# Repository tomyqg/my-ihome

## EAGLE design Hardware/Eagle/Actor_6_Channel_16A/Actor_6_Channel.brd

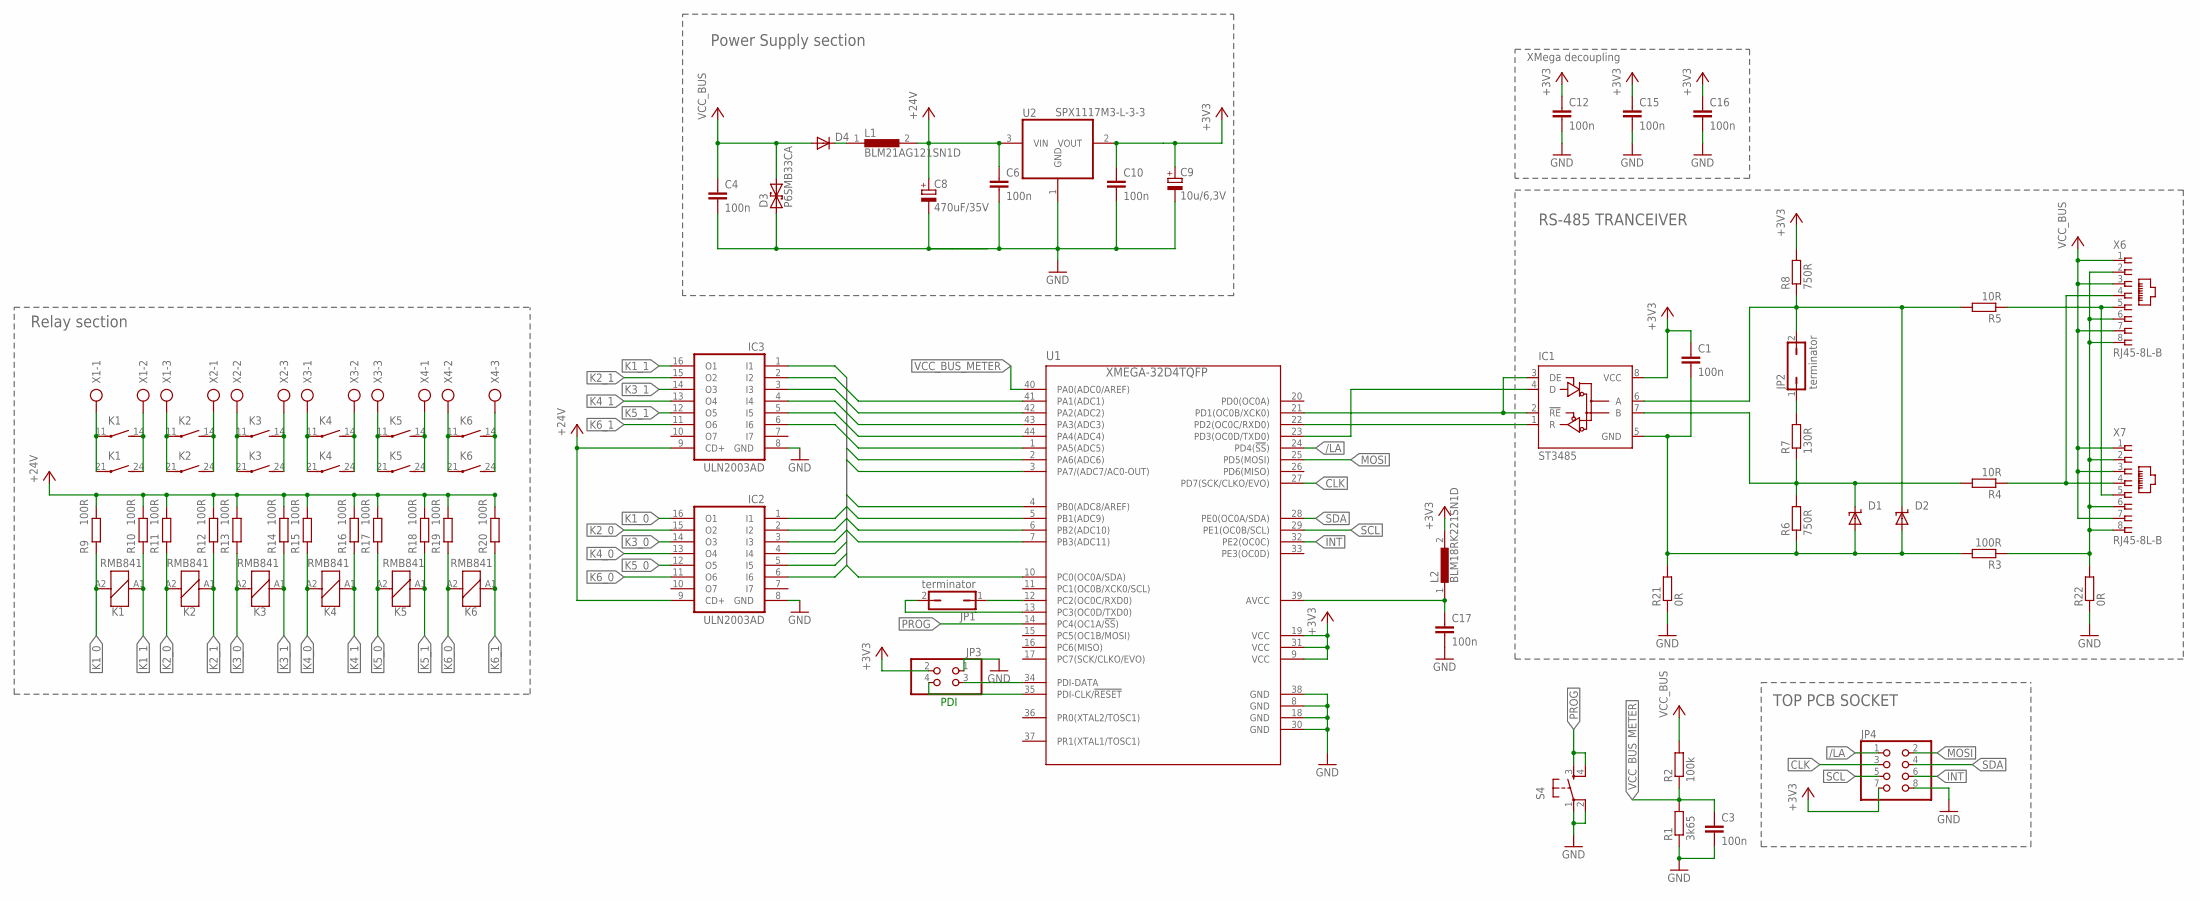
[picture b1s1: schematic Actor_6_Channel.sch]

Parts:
C1, C3, C4, C6, C10, C12, C15, C16, C17: 100n; C0603K
C8: 470uF/35V; E5-10,5
C9: 10u/6,3V; E2-4
D1, D2: SUPPRESSOR-SMBJ; SMBJ
D3: P6SMB33CA; DO214AA
D4: DIODE-DO214AA; DO214AA
IC1: ST3485; D_R-PDSO-G8
IC2, IC3: ULN2003AD; SO16
JP1, JP2: terminator; JP1
JP3: PINHD-2X2; 2X02
JP4: PINHD-2X4; 2X04
K1, K2, K3, K4, K5, K6: RMB841; RT2N/O
L1: BLM21AG121SN1D; 805
L2: BLM18RK221SN1D; 0603
R1: 3k65; R0603
R2: 100k; R0603
R3, R9, R10, R11, R12, R13, R14, R15, R16, R17, R18, R19, R20: 100R; R0603
R4, R5: 10R; R0603
R6: 750R; M1206
R7: 130R; R0603
R8: 750R; R0603
R21, R22: 0R; R0603
S4: SPARKFUN_TAC_SWITCHPTH; SPARKFUN_TACTILE-PTH
U1: XMEGA-32D4TQFP; TQFP44
U2: SPX1117M3-L-3-3; SOT223
X1, X2, X3, X4: MKDS_5/3-7,5; MKDS_5/-750
X6, X7: RJ45-8L-B; RJ45-NO-SHIELD

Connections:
+3V3: C1.1, C9.+, C10.1, C12.1, C15.1, C16.1, IC1.8 (VCC), JP3.2, JP4.7, L2.2, R8.2, U1.9 (VCC), U1.19 (VCC), U1.31 (VCC), U2.2 (VOUT)
+24V: C6.1, C8.+, IC2.9 (CD+), IC3.9 (CD+), L1.2, R9.2, R10.2, R11.2, R12.2, R13.2, R14.2, R15.2, R16.2, R17.2, R18.2, R19.2, R20.2, U2.3 (VIN)
/LA: JP4.1, U1.24 (PD4(!SS!))
A: R5.1, X6.5, X7.5
B: R4.1, X6.4, X7.4
CLK: JP4.3, U1.27 (PD7(SCK/CLKO/EVO))
DE_/RE: IC1.2 (!RE), IC1.3 (DE), U1.21 (PD1(OC0B/XCK0))
GND: C3.2, C4.2, C6.2, C8.-, C9.-, C10.2, C12.2, C15.2, C16.2, C17.2, D3.A (1), IC2.8 (GND), IC3.8 (GND), JP3.1, JP4.8, R1.1, R21.1, R22.1, S4.1, S4.2, U1.8 (GND), U1.18 (GND), U1.30 (GND), U1.38 (GND), U2.1 (GND)
INT: JP4.6, U1.32 (PE2(OC0C))
K1_0: IC2.16 (O1), K1.A2 (1), R9.1
K1_1: IC3.16 (O1), K1.A1 (2), R10.1
K2_0: IC2.15 (O2), K2.A2 (1), R11.1
K2_1: IC3.15 (O2), K2.A1 (2), R12.1
K3_0: IC2.14 (O3), K3.A2 (1), R13.1
K3_1: IC3.14 (O3), K3.A1 (2), R14.1
K4_0: IC2.13 (O4), K4.A2 (1), R15.1
K4_1: IC3.13 (O4), K4.A1 (2), R16.1
K5_0: IC2.12 (O5), K5.A2 (1), R17.1
K5_1: IC3.12 (O5), K5.A1 (2), R18.1
K6_0: IC2.11 (O6), K6.A2 (1), R19.1
K6_1: IC3.11 (O6), K6.A1 (2), R20.1
MOSI: JP4.2, U1.25 (PD5(MOSI))
unnamed: K1.11, K1.21, X1.1
unnamed: K6.11, K6.21, X4.2
unnamed: K2.14 (S), K2.24 (S), X2.1
unnamed: K2.11, K2.21, X1.3
unnamed: K3.11, K3.21, X2.2
unnamed: K3.14 (S), K3.24 (S), X2.3
unnamed: K4.11, K4.21, X3.1
unnamed: K5.11, K5.21, X3.3
unnamed: K5.14 (S), K5.24 (S), X4.1
unnamed: JP3.3, U1.34 (PDI-DATA)
unnamed: K6.14 (S), K6.24 (S), X4.3
unnamed: JP3.4, U1.35 (PDI-CLK/!RESET)
unnamed: JP2.1, R7.2
unnamed: D1.C, IC1.7 (B), R4.2, R6.2, R7.1
unnamed: D4.C, L1.1
unnamed: JP1.2, U1.13 (PC3(OC0D/TXD0))
unnamed: JP1.1, U1.12 (PC2(OC0C/RXD0))
unnamed: C17.1, L2.1, U1.39 (AVCC)
unnamed: C1.2, D1.A, D2.A, IC1.5 (GND), R3.2, R6.1, R21.2
unnamed: R3.1, R22.2, X6.2, X6.6, X6.8, X7.2, X7.6, X7.8
unnamed: K1.14 (S), K1.24 (S), X1.2
unnamed: K4.14 (S), K4.24 (S), X3.2
PA1: IC3.6 (I6), U1.41 (PA1(ADC1))
PA2: IC3.5 (I5), U1.42 (PA2(ADC2))
PA3: IC3.4 (I4), U1.43 (PA3(ADC3))
PA4: IC3.3 (I3), U1.44 (PA4(ADC4))
PA5: IC3.2 (I2), U1.1 (PA5(ADC5))
PA6: IC3.1 (I1), U1.2 (PA6(ADC6))
PA7: IC2.6 (I6), U1.3 (PA7/(ADC7/AC0-OUT))
PB0: IC2.5 (I5), U1.4 (PB0(ADC8/AREF))
PB1: IC2.4 (I4), U1.5 (PB1(ADC9))
PB2: IC2.3 (I3), U1.6 (PB2(ADC10))
PB3: IC2.2 (I2), U1.7 (PB3(ADC11))
PC0: IC2.1 (I1), U1.10 (PC0(OC0A/SDA))
PROG: S4.3, S4.4, U1.14 (PC4(OC1A/!SS!))
RS485_A1: D2.C, IC1.6 (A), JP2.2, R5.2, R8.1
RXD: IC1.1 (R), U1.22 (PD2(OC0C/RXD0))
SCL: JP4.5, U1.29 (PE1(OC0B/SCL))
SDA: JP4.4, U1.28 (PE0(OC0A/SDA))
TXD: IC1.4 (D), U1.23 (PD3(OC0D/TXD0))
VCC_BUS: C4.1, D3.C (2), D4.A, R2.2, X6.1, X6.3, X6.7, X7.1, X7.3, X7.7
VCC_BUS_METER: C3.1, R1.2, R2.1, U1.40 (PA0(ADC0/AREF))

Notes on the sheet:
Power Supply section
XMega decoupling
RS-485 TRANCEIVER
PDI
Relay section
TOP PCB SOCKET

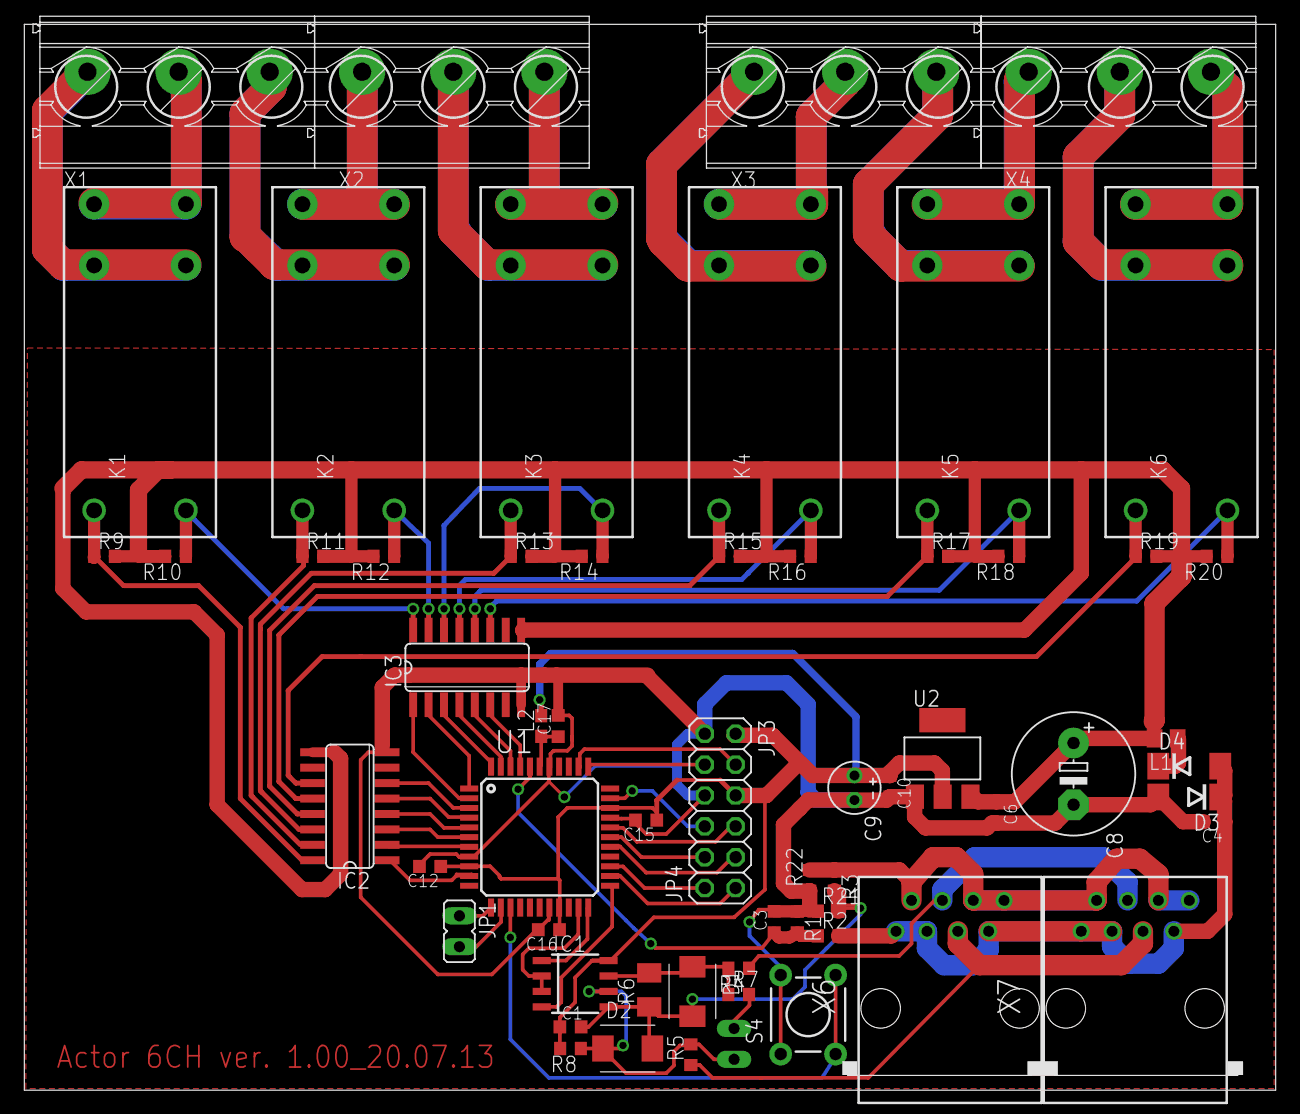
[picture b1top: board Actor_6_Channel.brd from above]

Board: 2 copper layers, 103.0 x 87.7 mm, 61 parts (1 on the bottom side), 64 nets.

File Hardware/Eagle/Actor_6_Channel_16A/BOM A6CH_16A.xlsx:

Part | Value | Package | Price (>100pcs) brutto | Supplier | %
C1 | 100n | C0603K | 2.5000000000000001E-2 | TME | 1.4651155976206517E-2
C2 | 470uF/35V | E5-10,5 | 0.27 | TME | 0.15823248454303038
C3 | 100n | C0603K | 2.5000000000000001E-2 | TME | 1.4651155976206517E-2
C4 | 100n | C0603K | 2.5000000000000001E-2 | TME | 1.4651155976206517E-2
C5 | 10u/6,3V | E2-5 | 5.7000000000000002E-2 | TME | 3.3404635625750856E-2
C6 | 100n | C0603K | 2.5000000000000001E-2 | TME | 1.4651155976206517E-2
C7 | 100n | C0603K | 2.5000000000000001E-2 | TME | 1.4651155976206517E-2
C8 | 100n | C0603K | 2.5000000000000001E-2 | TME | 1.4651155976206517E-2
C9 | 100n | C0603K | 2.5000000000000001E-2 | TME | 1.4651155976206517E-2
C10 | 100n | C0603K | 2.5000000000000001E-2 | TME | 1.4651155976206517E-2
C11 | 100n | C0603K | 2.5000000000000001E-2 | TME | 1.4651155976206517E-2
D1 | P6SMB6.8CA-LF | DO214AA | 0.5 | TME | 0.29302311952413035
D2 | P6SMB6.8CA-LF | DO214AA | 0.5 | TME | 0.29302311952413035
D3 | P6SMB33CA | DO214AA | 0.43 | TME | 0.25199988279075208
D4 |  | DO214AA | 0.1 | TME | 5.860462390482607E-2
IC1 | ST3485 | D_R-PDSO-G8 | 3.3 | TME | 1.9339525888592599
IC2 | ULN2003AD | SO16 | 0.72 | TME | 0.42195329211474769
IC3 | ULN2003AD | SO16 | 0.72 | TME | 0.42195329211474769
JP1 | terminator | JP1 | 6.8000000000000005E-2 | TME | 3.9851144255281724E-2
JP2 | terminator | JP1 | 6.8000000000000005E-2 | TME | 3.9851144255281724E-2
JP3 |  | 2X02 | 0.13600000000000001 | TME | 7.9702288510563449E-2
JP4 |  | 2X04 | 0.27200000000000002 | TME | 0.1594045770211269
K1 | RMB841 | RT2N/O | 14.32 | piekarz | 8.3921821431710928
K2 | RMB841 | RT2N/O | 14.32 | piekarz | 8.3921821431710928
K3 | RMB841 | RT2N/O | 14.32 | piekarz | 8.3921821431710928
K4 | RMB841 | RT2N/O | 14.32 | piekarz | 8.3921821431710928
K5 | RMB841 | RT2N/O | 14.32 | piekarz | 8.3921821431710928
K6 | RMB841 | RT2N/O | 14.32 | piekarz | 8.3921821431710928
L1 | BLM21AG121 | 805 | 0.222 | TME | 0.13010226506871386
L2 | BLM18RK221 | 603 | 9.7000000000000003E-2 | TME | 5.6846485187681289E-2
R1 | 3k65 | R0603 | 2.5000000000000001E-2 | TME | 1.4651155976206517E-2
R2 | 100k | R0603 | 2.5000000000000001E-2 | TME | 1.4651155976206517E-2
R3 | 100R | R0603 | 2.5000000000000001E-2 | TME | 1.4651155976206517E-2
R4 | 10R | R0603 | 2.5000000000000001E-2 | TME | 1.4651155976206517E-2
R5 | 10R | R0603 | 2.5000000000000001E-2 | TME | 1.4651155976206517E-2
R6 | 750R | M1206 | 2.5000000000000001E-2 | TME | 1.4651155976206517E-2
R7 | 130R | R0603 | 2.5000000000000001E-2 | TME | 1.4651155976206517E-2
R8 | 750R | R0603 | 2.5000000000000001E-2 | TME | 1.4651155976206517E-2
R9 | 100R | R0603 | 2.5000000000000001E-2 | TME | 1.4651155976206517E-2
R10 | 100R | R0603 | 2.5000000000000001E-2 | TME | 1.4651155976206517E-2
R11 | 100R | R0603 | 2.5000000000000001E-2 | TME | 1.4651155976206517E-2
R12 | 100R | R0603 | 2.5000000000000001E-2 | TME | 1.4651155976206517E-2
R13 | 100R | R0603 | 2.5000000000000001E-2 | TME | 1.4651155976206517E-2
R14 | 100R | R0603 | 2.5000000000000001E-2 | TME | 1.4651155976206517E-2
R15 | 100R | R0603 | 2.5000000000000001E-2 | TME | 1.4651155976206517E-2
R16 | 100R | R0603 | 2.5000000000000001E-2 | TME | 1.4651155976206517E-2
R17 | 100R | R0603 | 2.5000000000000001E-2 | TME | 1.4651155976206517E-2
R18 | 100R | R0603 | 2.5000000000000001E-2 | TME | 1.4651155976206517E-2
R19 | 100R | R0603 | 2.5000000000000001E-2 | TME | 1.4651155976206517E-2
R20 | 100R | R0603 | 2.5000000000000001E-2 | TME | 1.4651155976206517E-2
R21 | 0R | R0603 | 2.5000000000000001E-2 | TME | 1.4651155976206517E-2
R22 | 0R | R0603 | 2.5000000000000001E-2 | TME | 1.4651155976206517E-2
S4 |  | NINIGI TACTM-619P-F | 0.24 | TME | 0.14065109737158255
U1 | XMEGA-32D4 | TQFP44 | 9.6300000000000008 | TME | 5.6436252820347503
U2 | SPX1117M3- | SOT223 | 0.63 | TME | 0.36920913060040422
X1 |  | TB-7.5-3P | 0.63 | TME | 0.36920913060040422
X2 |  | TB-7.5-3P | 0.63 | TME | 0.36920913060040422
X3 |  | TB-7.5-3P | 0.63 | TME | 0.36920913060040422
X4 |  | TB-7.5-3P | 0.63 | TME | 0.36920913060040422
X5 | RJ45-8L-B | RJ45-NO-SHIELD | 1.61 | TME | 0.94353444486769966
X6 | RJ45-8L-B | RJ45-NO-SHIELD | 1.61 | TME | 0.94353444486769966
Case |  | MODULBOX | 39.24 | TME | 22.996454420253748
PCB |  |  | 21 | drukowane.pl | 12.306971020013474
 |  | amount | 170.63500000000008

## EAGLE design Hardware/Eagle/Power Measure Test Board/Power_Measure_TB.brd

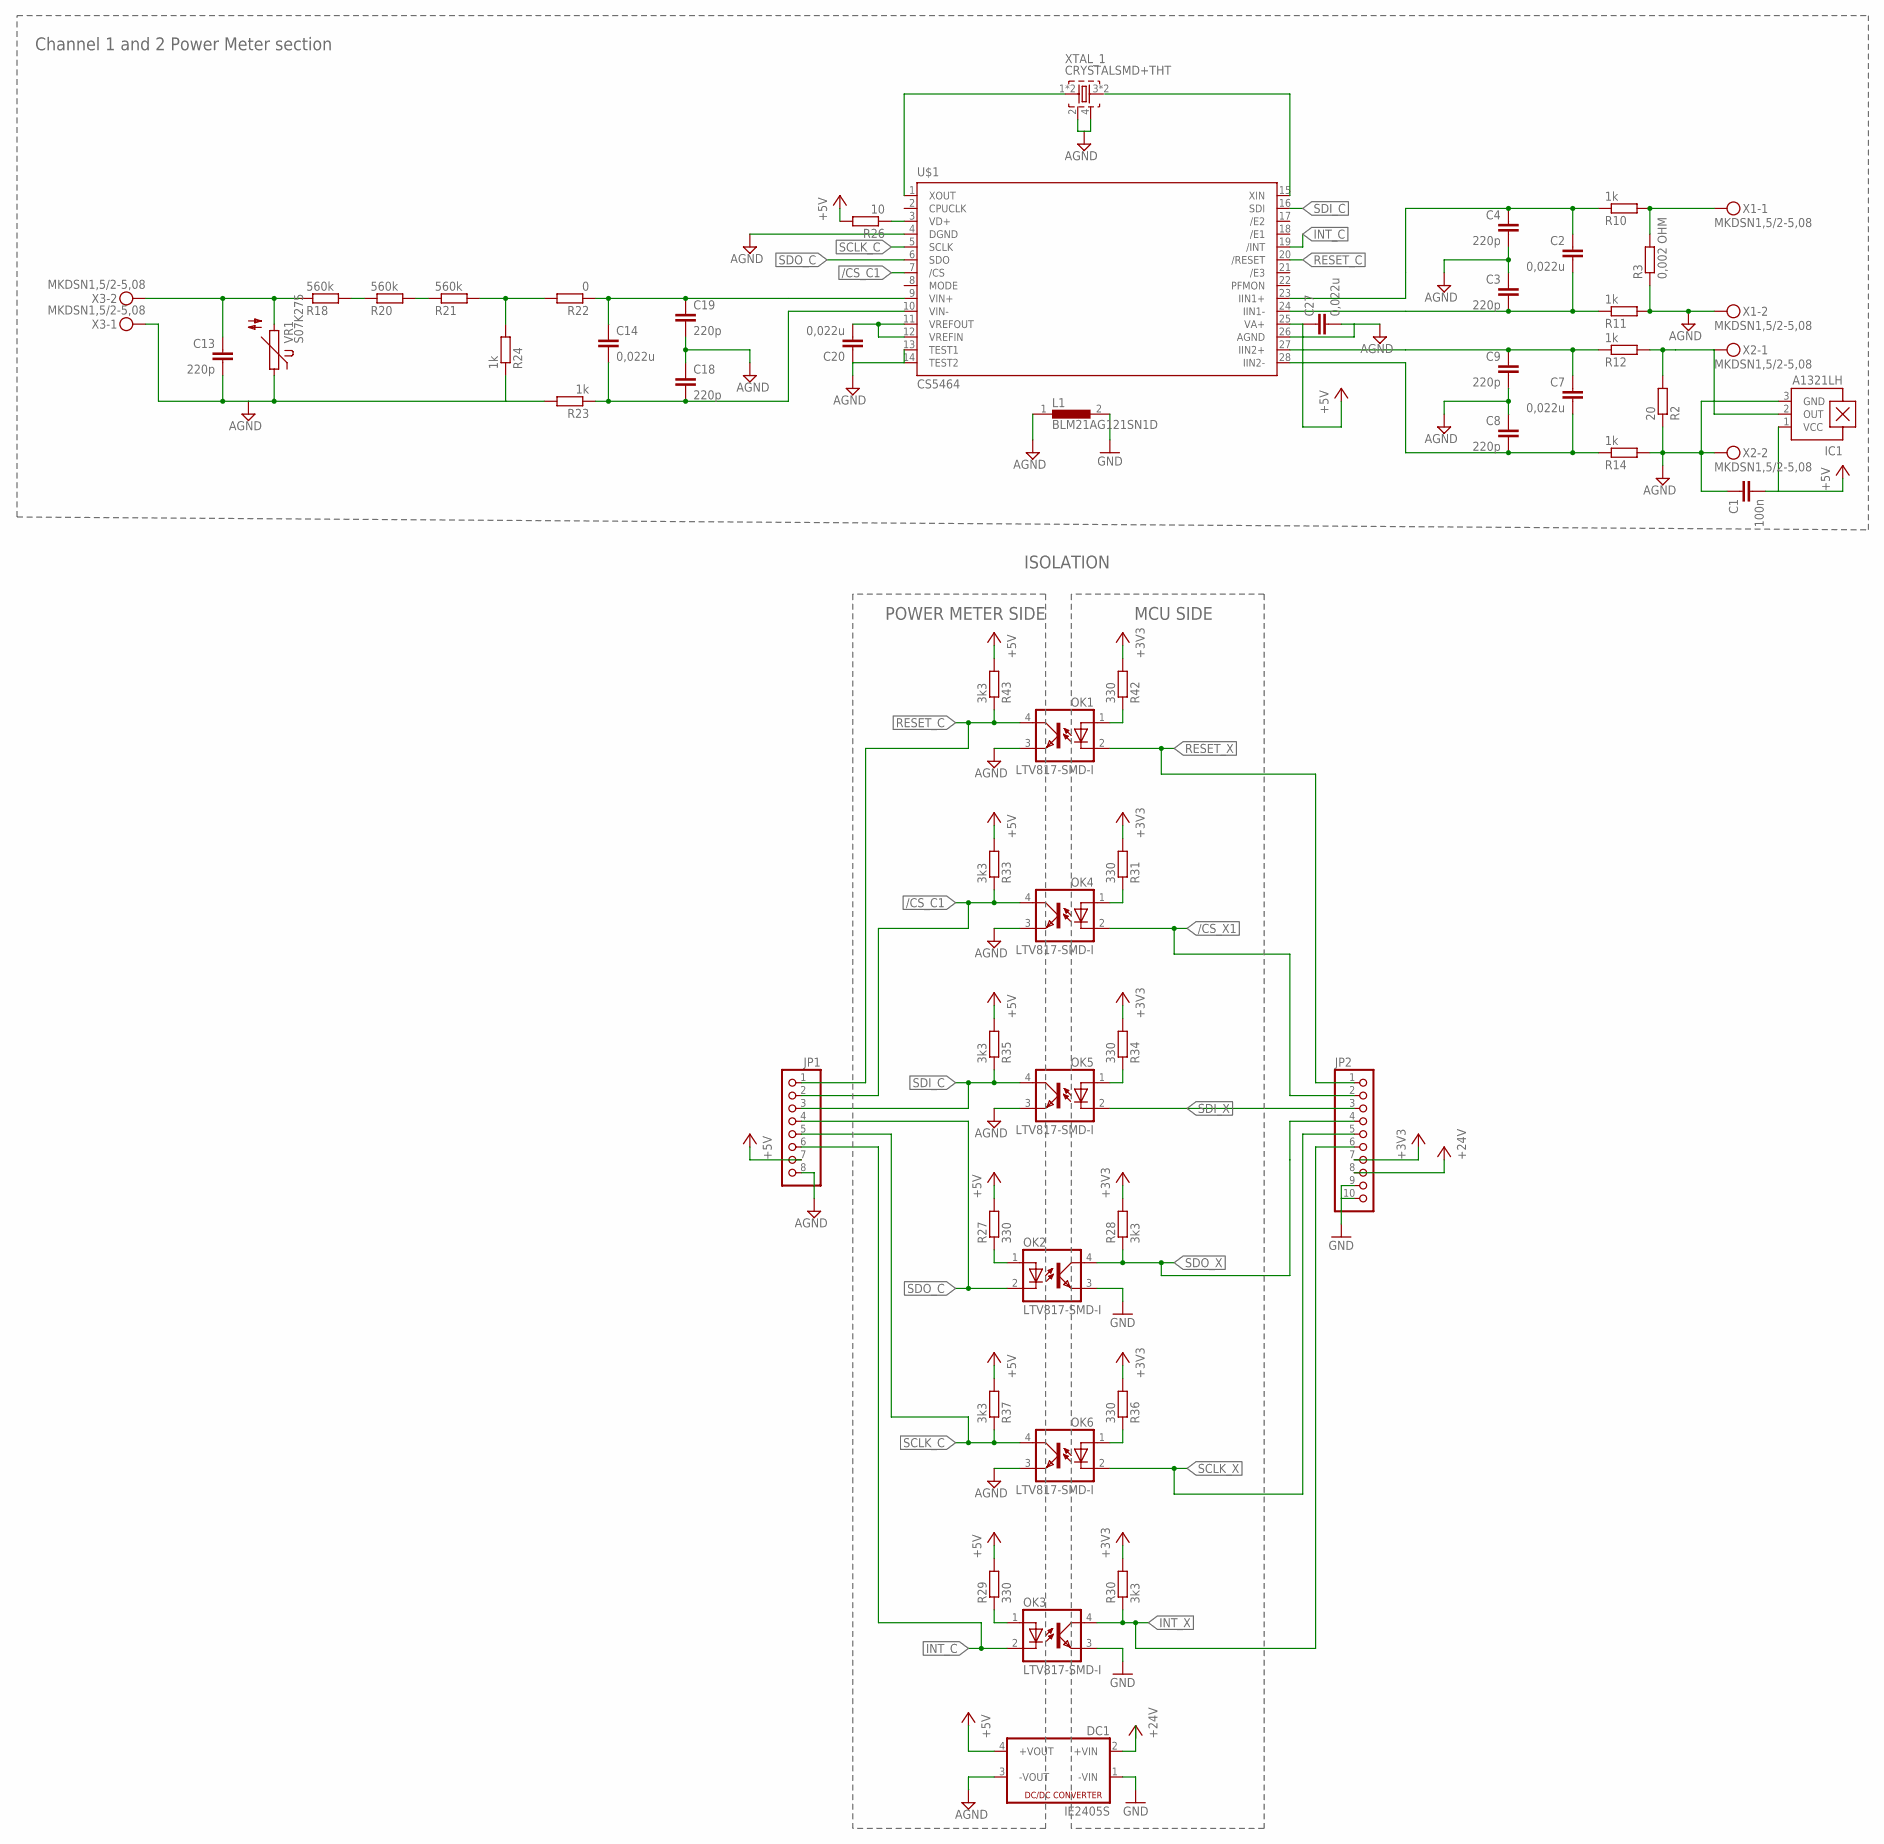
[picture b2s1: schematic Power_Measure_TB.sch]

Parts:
C1: 100n; C0603K
C2, C7, C14, C20, C27: 0,022u; C0603K
C3, C4, C8, C9, C13, C18, C19: 220p; C0603K
DC1: IE2405S; 4SIL
IC1: A1321LH; SOT23-W
JP1: PINHD-1X8; 1X08
JP2: PINHD-1X10; 1X10
L1: BLM21AG121SN1D; 805
OK1, OK2, OK3, OK4, OK5, OK6: LTV817-SMD-I; SMD4
R2: 20; R0603
R3: 0,002 OHM; R2512
R10, R11, R12, R14, R23, R24: 1k; R0603
R18, R20, R21: 560k; R0603
R22: 0; R0603
R26: 10; R0603
R27, R29, R31, R34, R36, R42: 330; M0805
R28, R30, R33, R35, R37, R43: 3k3; M0805
U$1: CS5464; SSOP-28L
VR1: S07K275
X1, X2, X3: MKDSN1,5/2-5,08
XTAL_1: CRYSTALSMD+THT; CRYSTAL20H+MT38

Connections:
+3V3: C1.2, IC1.1 (VCC), JP1.7, JP2.7, R28.2, R30.2, R31.2, R34.2, R36.2, R42.2
+5V: C27.1, DC1.4 (+VOUT), R26.2, R27.2, R29.2, R33.2, R35.2, R37.2, R43.2, U$1.25 (VA+)
/CS_C1: JP1.2, OK4.4 (COL), R33.1, U$1.7 (/CS)
/CS_X1: JP2.2, OK4.2 (C)
AGND: C1.1, C3.1, C4.2, C8.1, C9.2, C13.2, C18.1, C19.2, C20.1, C27.2, DC1.3 (-VOUT), IC1.3 (GND), JP1.8, L1.1, OK1.3 (EMIT), OK4.3 (EMIT), OK5.3 (EMIT), OK6.3 (EMIT), R2.1, R3.1, R11.2, R14.2, R23.2, R24.1, U$1.4 (DGND), U$1.13 (TEST1), U$1.14 (TEST2), U$1.26 (AGND), VR1.1, X1.2, X2.2, X3.1, XTAL_1.2, XTAL_1.4
GND: DC1.1 (-VIN), JP2.9, JP2.10, L1.2, OK2.3 (EMIT), OK3.3 (EMIT)
INT_C: JP1.6, OK3.2 (C), U$1.19 (/INT)
INT_X: JP2.6, OK3.4 (COL), R30.1
MODE: U$1.8 (MODE)
unnamed: R18.2, R20.1
unnamed: C7.2, C8.2, R14.1, U$1.28 (IIN2-)
unnamed: C2.2, C3.2, R11.1, U$1.24 (IIN1-)
unnamed: C13.1, R18.1, VR1.2, X3.2
unnamed: C2.1, C4.1, R10.1, U$1.23 (IIN1+)
unnamed: R26.1, U$1.3 (VD+)
unnamed: C20.2, U$1.11 (VREFOUT), U$1.12 (VREFIN)
unnamed: OK1.1 (A), R42.1
unnamed: OK2.1 (A), R27.1
unnamed: OK3.1 (A), R29.1
unnamed: OK4.1 (A), R31.1
unnamed: IC1.2 (OUT), R2.2, X2.1
unnamed: R3.2, R10.2, X1.1
unnamed: C7.1, C9.1, R12.1, U$1.27 (IIN2+)
unnamed: U$1.1 (XOUT), XTAL_1.1, XTAL_1.1_T (1)
unnamed: R20.2, R21.1
unnamed: C14.2, C18.2, R23.1, U$1.10 (VIN-)
unnamed: C14.1, C19.1, R22.1, U$1.9 (VIN+)
unnamed: OK5.1 (A), R34.1
unnamed: R21.2, R22.2, R24.2
unnamed: OK6.1 (A), R36.1
RESET_C: JP1.1, OK1.4 (COL), R43.1, U$1.20 (/RESET)
RESET_X: JP2.1, OK1.2 (C)
SCLK_C: JP1.5, OK6.4 (COL), R37.1, U$1.5 (SCLK)
SCLK_X: JP2.5, OK6.2 (C)
SDI_C: JP1.3, OK5.4 (COL), R35.1, U$1.16 (SDI)
SDI_X: JP2.3, OK5.2 (C)
SDO_C: JP1.4, OK2.2 (C), U$1.6 (SDO)
SDO_X: JP2.4, OK2.4 (COL), R28.1
VCC: DC1.2 (+VIN), JP2.8

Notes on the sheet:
Channel 1 and 2 Power Meter section
ISOLATION
POWER METER SIDE
MCU SIDE

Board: 2 copper layers, 55 parts (0 on the bottom side), 38 nets, no tracks yet.

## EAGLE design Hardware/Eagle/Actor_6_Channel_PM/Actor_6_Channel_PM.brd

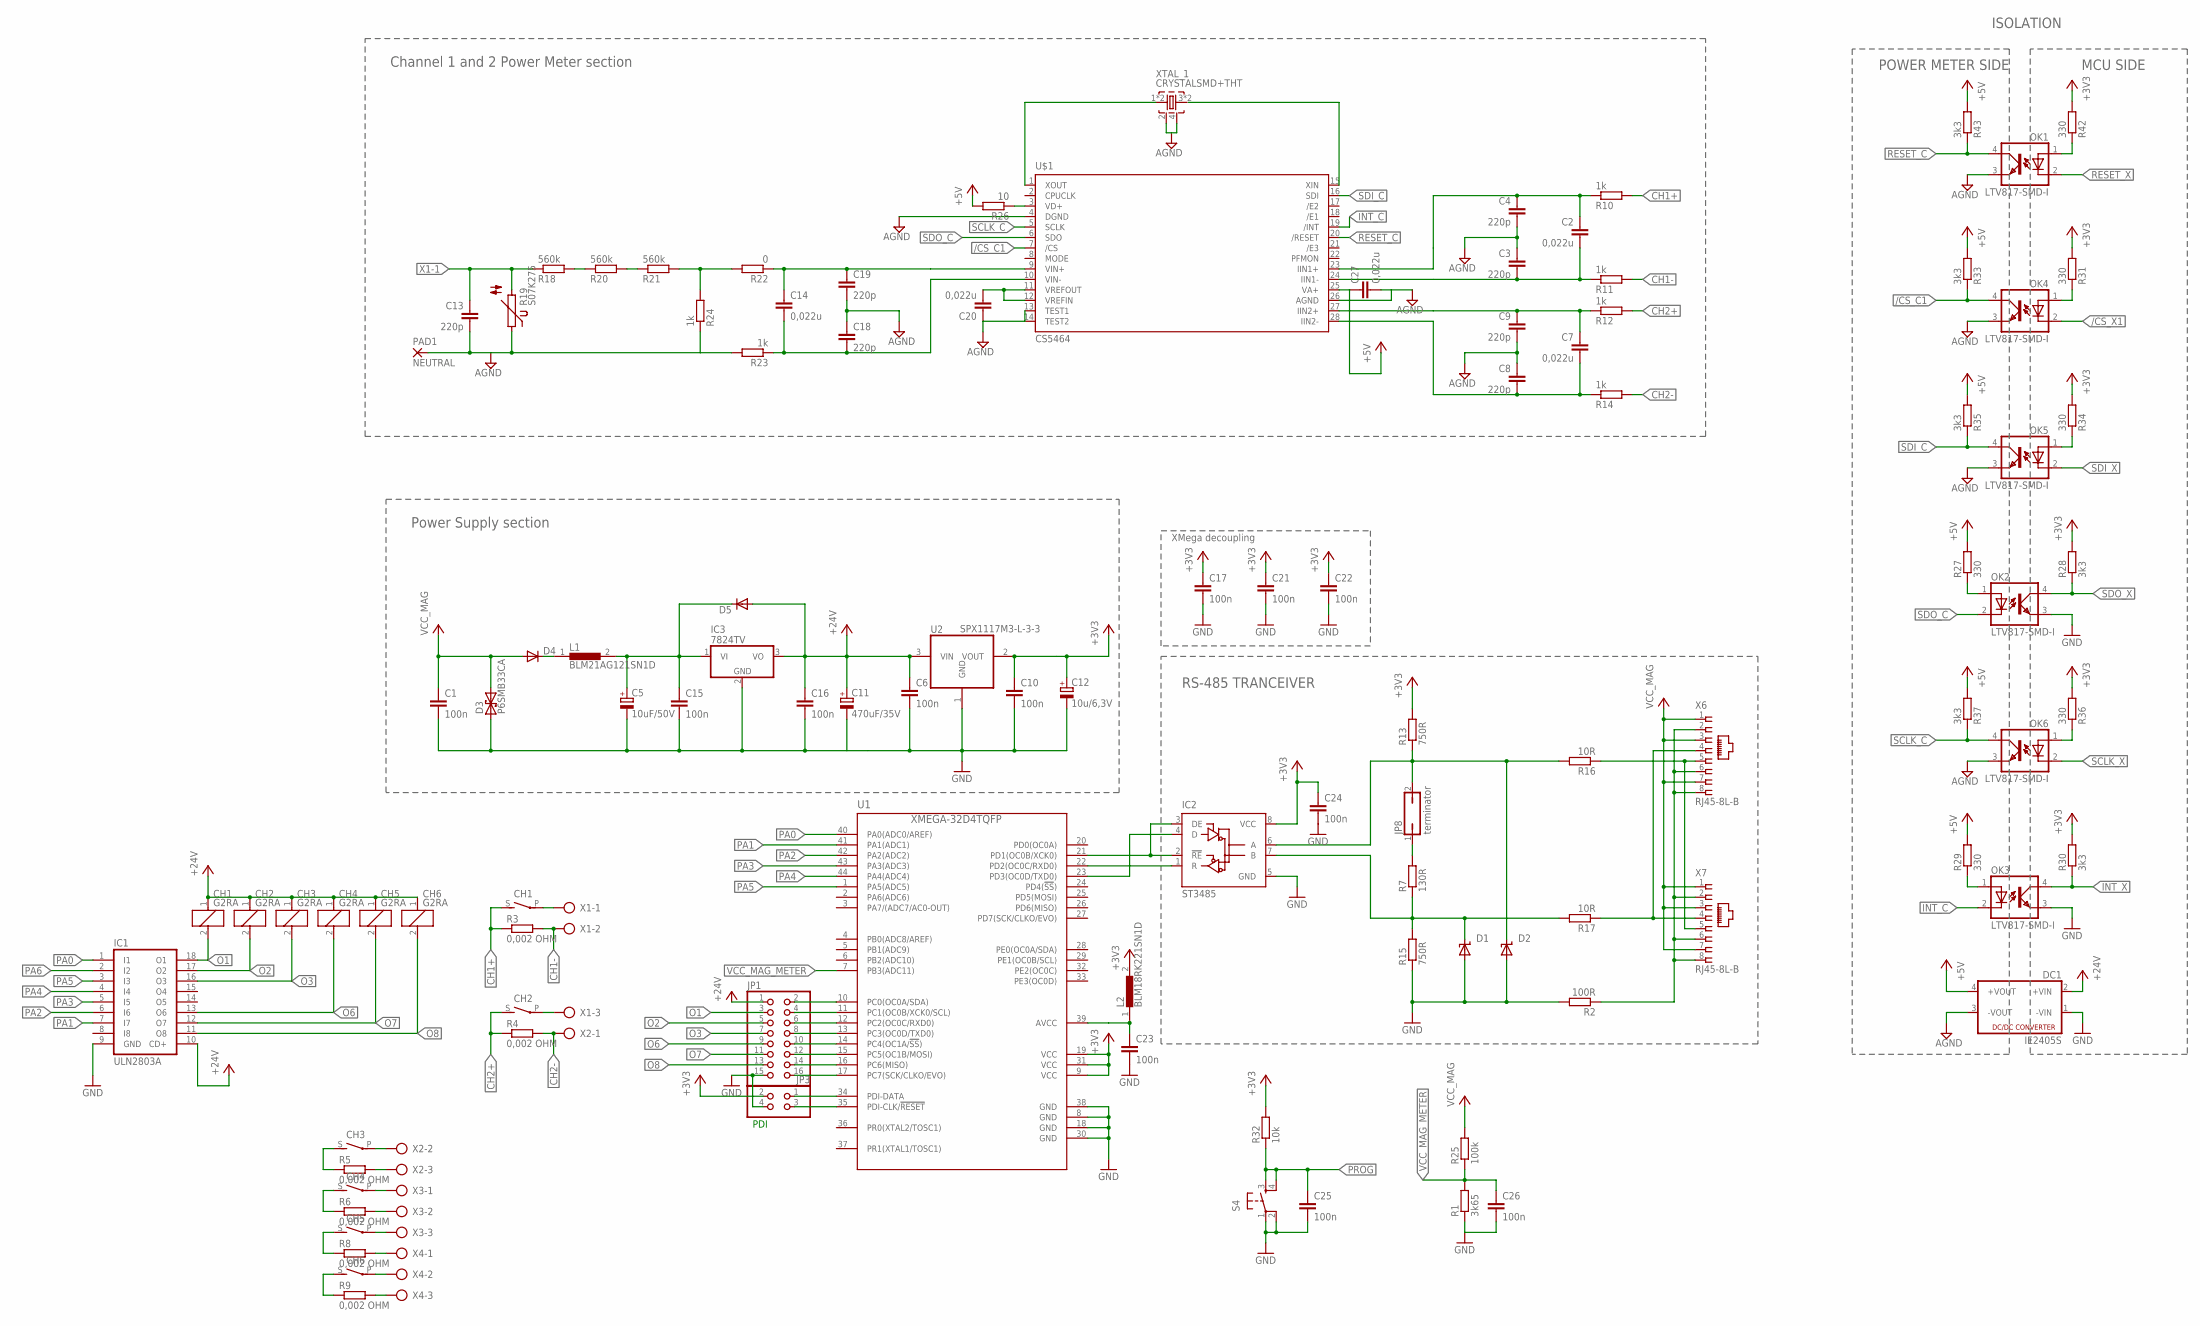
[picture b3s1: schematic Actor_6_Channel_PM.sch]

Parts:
C1, C6, C10, C15, C16, C17, C21, C22, C23, C24: 100n; C0603K
C2, C7, C14, C20, C27: 0,022u; C0603K
C3, C4, C8, C9, C13, C18, C19: 220p; C0603K
C5: 10uF/50V; E2,5-5
C11: 470uF/35V; E5-10,5
C12: 10u/6,3V; E2-4
C25, C26: 100n; C0603
CH1, CH2, CH3, CH4, CH5, CH6: G2RA
D1, D2: SUPPRESSOR-SMBJ; SMBJ
D3: P6SMB33CA; DO214AA
D4, D5: DIODE-DO214AA; DO214AA
DC1: IE2405S; 4SIL
IC1: ULN2803A; SO18W
IC2: ST3485; D_R-PDSO-G8
IC3: 7824TV; TO220V
JP1: PINHD-2X8; 2X08
JP3: PINHD-2X2; 2X02
JP8: terminator; JP1
L1: BLM21AG121SN1D; 805
L2: BLM18RK221SN1D; 0603
OK1, OK2, OK3, OK4, OK5, OK6: LTV817-SMD-I; SMD4
PAD1: NEUTRAL; 2,54/1,0
R1: 3k65; R0603
R2: 100R; R0603
R3, R4, R5, R6, R8, R9: 0,002 OHM; R2512
R7: 130R; R0603
R10, R11, R12, R14, R23, R24: 1k; R0603
R13: 750R; R0603
R15: 750R; M1206
R16, R17: 10R; R0603
R18, R20, R21: 560k; R0603
R19: S07K275
R22: 0; R0603
R25: 100k; R0603
R26: 10; R0603
R27, R29, R31, R34, R36, R42: 330; M0805
R28, R30, R33, R35, R37, R43: 3k3; M0805
R32: 10k; R0603
S4: SPARKFUN_TAC_SWITCHPTH; SPARKFUN_TACTILE-PTH
U1: XMEGA-32D4TQFP; TQFP44
U2: SPX1117M3-L-3-3; SOT223
U$1: CS5464; SSOP-28L
X1, X2, X3, X4: MKDS_5/3-7,5; MKDS_5/-750
X6, X7: RJ45-8L-B; RJ45-NO-SHIELD
XTAL_1: CRYSTALSMD+THT; CRYSTAL20H+MT38

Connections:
+3V3: C10.1, C12.+, C17.1, C21.1, C22.1, C24.1, IC2.8 (VCC), JP3.2, L2.2, R13.2, R28.2, R30.2, R31.2, R32.2, R34.2, R36.2, R42.2, U1.9 (VCC), U1.19 (VCC), U1.31 (VCC), U2.2 (VOUT)
+5V: C27.1, DC1.4 (+VOUT), R26.2, R27.2, R29.2, R33.2, R35.2, R37.2, R43.2, U$1.25 (VA+)
+24V: C6.1, C11.+, C16.1, CH1.1, CH2.1, CH3.1, CH4.1, CH5.1, CH6.1, D5.A, IC1.10 (CD+), IC3.3 (VO), U2.3 (VIN)
/CS_C1: OK4.4 (COL), R33.1, U$1.7 (/CS)
/CS_X1: OK4.2 (C)
A: R16.1, X6.5, X7.5
AGND: C3.1, C4.2, C8.1, C9.2, C13.2, C18.1, C19.2, C20.1, C27.2, DC1.3 (-VOUT), OK1.3 (EMIT), OK4.3 (EMIT), OK5.3 (EMIT), OK6.3 (EMIT), PAD1.1, R19.1, R23.2, R24.1, U$1.4 (DGND), U$1.13 (TEST1), U$1.14 (TEST2), U$1.26 (AGND), XTAL_1.2, XTAL_1.4
B: R17.1, X6.4, X7.4
CH1+: CH1.S, R3.1, R10.2
CH1-: R3.2, R11.2, X1.2
CH2+: CH2.S, R4.1, R12.2
CH2-: R4.2, R14.2, X2.1
GND: C1.2, C5.-, C6.2, C10.2, C11.-, C12.-, C15.2, C16.2, C17.2, C21.2, C22.2, C23.2, C24.2, C25.2, C26.2, D1.A, D2.A, D3.A (1), DC1.1 (-VIN), IC1.9 (GND), IC2.5 (GND), IC3.2 (GND), JP1.15, JP3.4, OK2.3 (EMIT), OK3.3 (EMIT), R1.1, R2.2, R15.1, S4.1, S4.2, U1.8 (GND), U1.18 (GND), U1.30 (GND), U1.38 (GND), U2.1 (GND)
GND_RS485: R2.1, X6.2, X6.6, X6.8, X7.2, X7.6, X7.8
INT_C: OK3.2 (C), U$1.19 (/INT)
INT_X: OK3.4 (COL), R30.1
MODE: U$1.8 (MODE)
unnamed: R18.2, R20.1
unnamed: C7.2, C8.2, R14.1, U$1.28 (IIN2-)
unnamed: CH2.P, X1.3
unnamed: C2.2, C3.2, R11.1, U$1.24 (IIN1-)
unnamed: CH3.P, X2.2
unnamed: C2.1, C4.1, R10.1, U$1.23 (IIN1+)
unnamed: R26.1, U$1.3 (VD+)
unnamed: C20.2, U$1.11 (VREFOUT), U$1.12 (VREFIN)
unnamed: OK1.1 (A), R42.1
unnamed: OK2.1 (A), R27.1
unnamed: OK3.1 (A), R29.1
unnamed: OK4.1 (A), R31.1
unnamed: CH4.P, X3.1
unnamed: C5.+, C15.1, D5.C, IC3.1 (VI), L1.2
unnamed: JP8.1, R7.2
unnamed: D1.C, IC2.7 (B), R7.1, R15.2, R17.2
unnamed: D4.C, L1.1
unnamed: C7.1, C9.1, R12.1, U$1.27 (IIN2+)
unnamed: CH5.P, X3.3
unnamed: CH3.S, R5.1
unnamed: CH6.P, X4.2
unnamed: R5.2, X2.3
unnamed: CH4.S, R6.1
unnamed: IC2.2 (!RE), IC2.3 (DE), U1.21 (PD1(OC0B/XCK0))
unnamed: IC2.4 (D), U1.23 (PD3(OC0D/TXD0))
unnamed: IC2.1 (R), U1.22 (PD2(OC0C/RXD0))
unnamed: R6.2, X3.2
unnamed: CH5.S, R8.1
unnamed: R8.2, X4.1
unnamed: CH6.S, R9.1
unnamed: R9.2, X4.3
unnamed: U$1.1 (XOUT), XTAL_1.1, XTAL_1.1_T (1)
unnamed: R20.2, R21.1
unnamed: C14.2, C18.2, R23.1, U$1.10 (VIN-)
unnamed: C14.1, C19.1, R22.1, U$1.9 (VIN+)
unnamed: OK5.1 (A), R34.1
unnamed: R21.2, R22.2, R24.2
unnamed: OK6.1 (A), R36.1
unnamed: JP1.16, U1.17 (PC7(SCK/CLKO/EVO))
unnamed: JP1.14, U1.16 (PC6(MISO))
unnamed: JP1.12, U1.15 (PC5(OC1B/MOSI))
unnamed: JP1.10, U1.14 (PC4(OC1A/!SS!))
unnamed: JP1.8, U1.13 (PC3(OC0D/TXD0))
unnamed: JP1.6, U1.12 (PC2(OC0C/RXD0))
unnamed: JP1.4, U1.11 (PC1(OC0B/XCK0/SCL))
unnamed: JP1.2, U1.10 (PC0(OC0A/SDA))
unnamed: JP3.1, U1.34 (PDI-DATA)
unnamed: JP3.3, U1.35 (PDI-CLK/!RESET)
unnamed: C23.1, L2.1, U1.39 (AVCC)
O1: CH1.2, IC1.18 (O1), JP1.3
O2: CH2.2, IC1.17 (O2), JP1.5
O3: CH3.2, IC1.16 (O3), JP1.7
O6: CH4.2, IC1.13 (O6), JP1.9
O7: CH5.2, IC1.12 (O7), JP1.11
O8: CH6.2, IC1.11 (O8), JP1.13
PA0: IC1.1 (I1), U1.40 (PA0(ADC0/AREF))
PA1: IC1.7 (I7), U1.41 (PA1(ADC1))
PA2: IC1.6 (I6), U1.42 (PA2(ADC2))
PA3: IC1.5 (I5), U1.43 (PA3(ADC3))
PA4: IC1.4 (I4), U1.44 (PA4(ADC4))
PA5: IC1.3 (I3), U1.1 (PA5(ADC5))
PA6: IC1.2 (I2)
PROG: C25.1, R32.1, S4.3, S4.4
RESET_C: OK1.4 (COL), R43.1, U$1.20 (/RESET)
RESET_X: OK1.2 (C)
RS485_A1: D2.C, IC2.6 (A), JP8.2, R13.1, R16.2
SCLK_C: OK6.4 (COL), R37.1, U$1.5 (SCLK)
SCLK_X: OK6.2 (C)
SDI_C: OK5.4 (COL), R35.1, U$1.16 (SDI)
SDI_X: OK5.2 (C)
SDO_C: OK2.2 (C), U$1.6 (SDO)
SDO_X: OK2.4 (COL), R28.1
VCC: C1.1, D3.C (2), D4.A, DC1.2 (+VIN), JP1.1
VCC_MAG: R25.2, X6.1, X6.3, X6.7, X7.1, X7.3, X7.7
VCC_MAG_METER: C26.1, R1.2, R25.1, U1.7 (PB3(ADC11))
X1-1: C13.1, CH1.P, R18.1, R19.2, X1.1

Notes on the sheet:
Power Supply section
XMega decoupling
RS-485 TRANCEIVER
PDI
Channel 1 and 2 Power Meter section
ISOLATION
POWER METER SIDE
MCU SIDE

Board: 2 copper layers, 104 parts (17 on the bottom side), 87 nets, no tracks yet.
